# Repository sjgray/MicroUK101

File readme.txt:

MicroUK101
==========

 This is a project to design a board for Grant Searle's Micro UK-101 design.
I started this in 2016 when I was very new at electronics and Kicad.
As I was interested in 6502 and OSI machines I picked this as something to
learn a bit of both things. When I finished the design in Sept 2016 I
ultimately decided not to make boards as I felt I would not really use the
board for anything serious. But it helped spur my interest in designing
more boards. I published the project on my web page and mostly forgot about
it.

 In 2022 I was contacted by someone interested in making the board so I
sent them all the files. Well, they made a run and the board worked with
only one (important) mistake... The power connector was backwards. So, I
have decided to fix that and update a few thing using the latest Kicad
and to put the files on Github for anyone interested in making their own
boards.

You can find my project webpage here:

http://www.cbmsteve.ca/microuk101/index.html

Gerbers files can be found in the Gerbers directory. I have not actually
made boards from these files, so use at your own risk!

Steve

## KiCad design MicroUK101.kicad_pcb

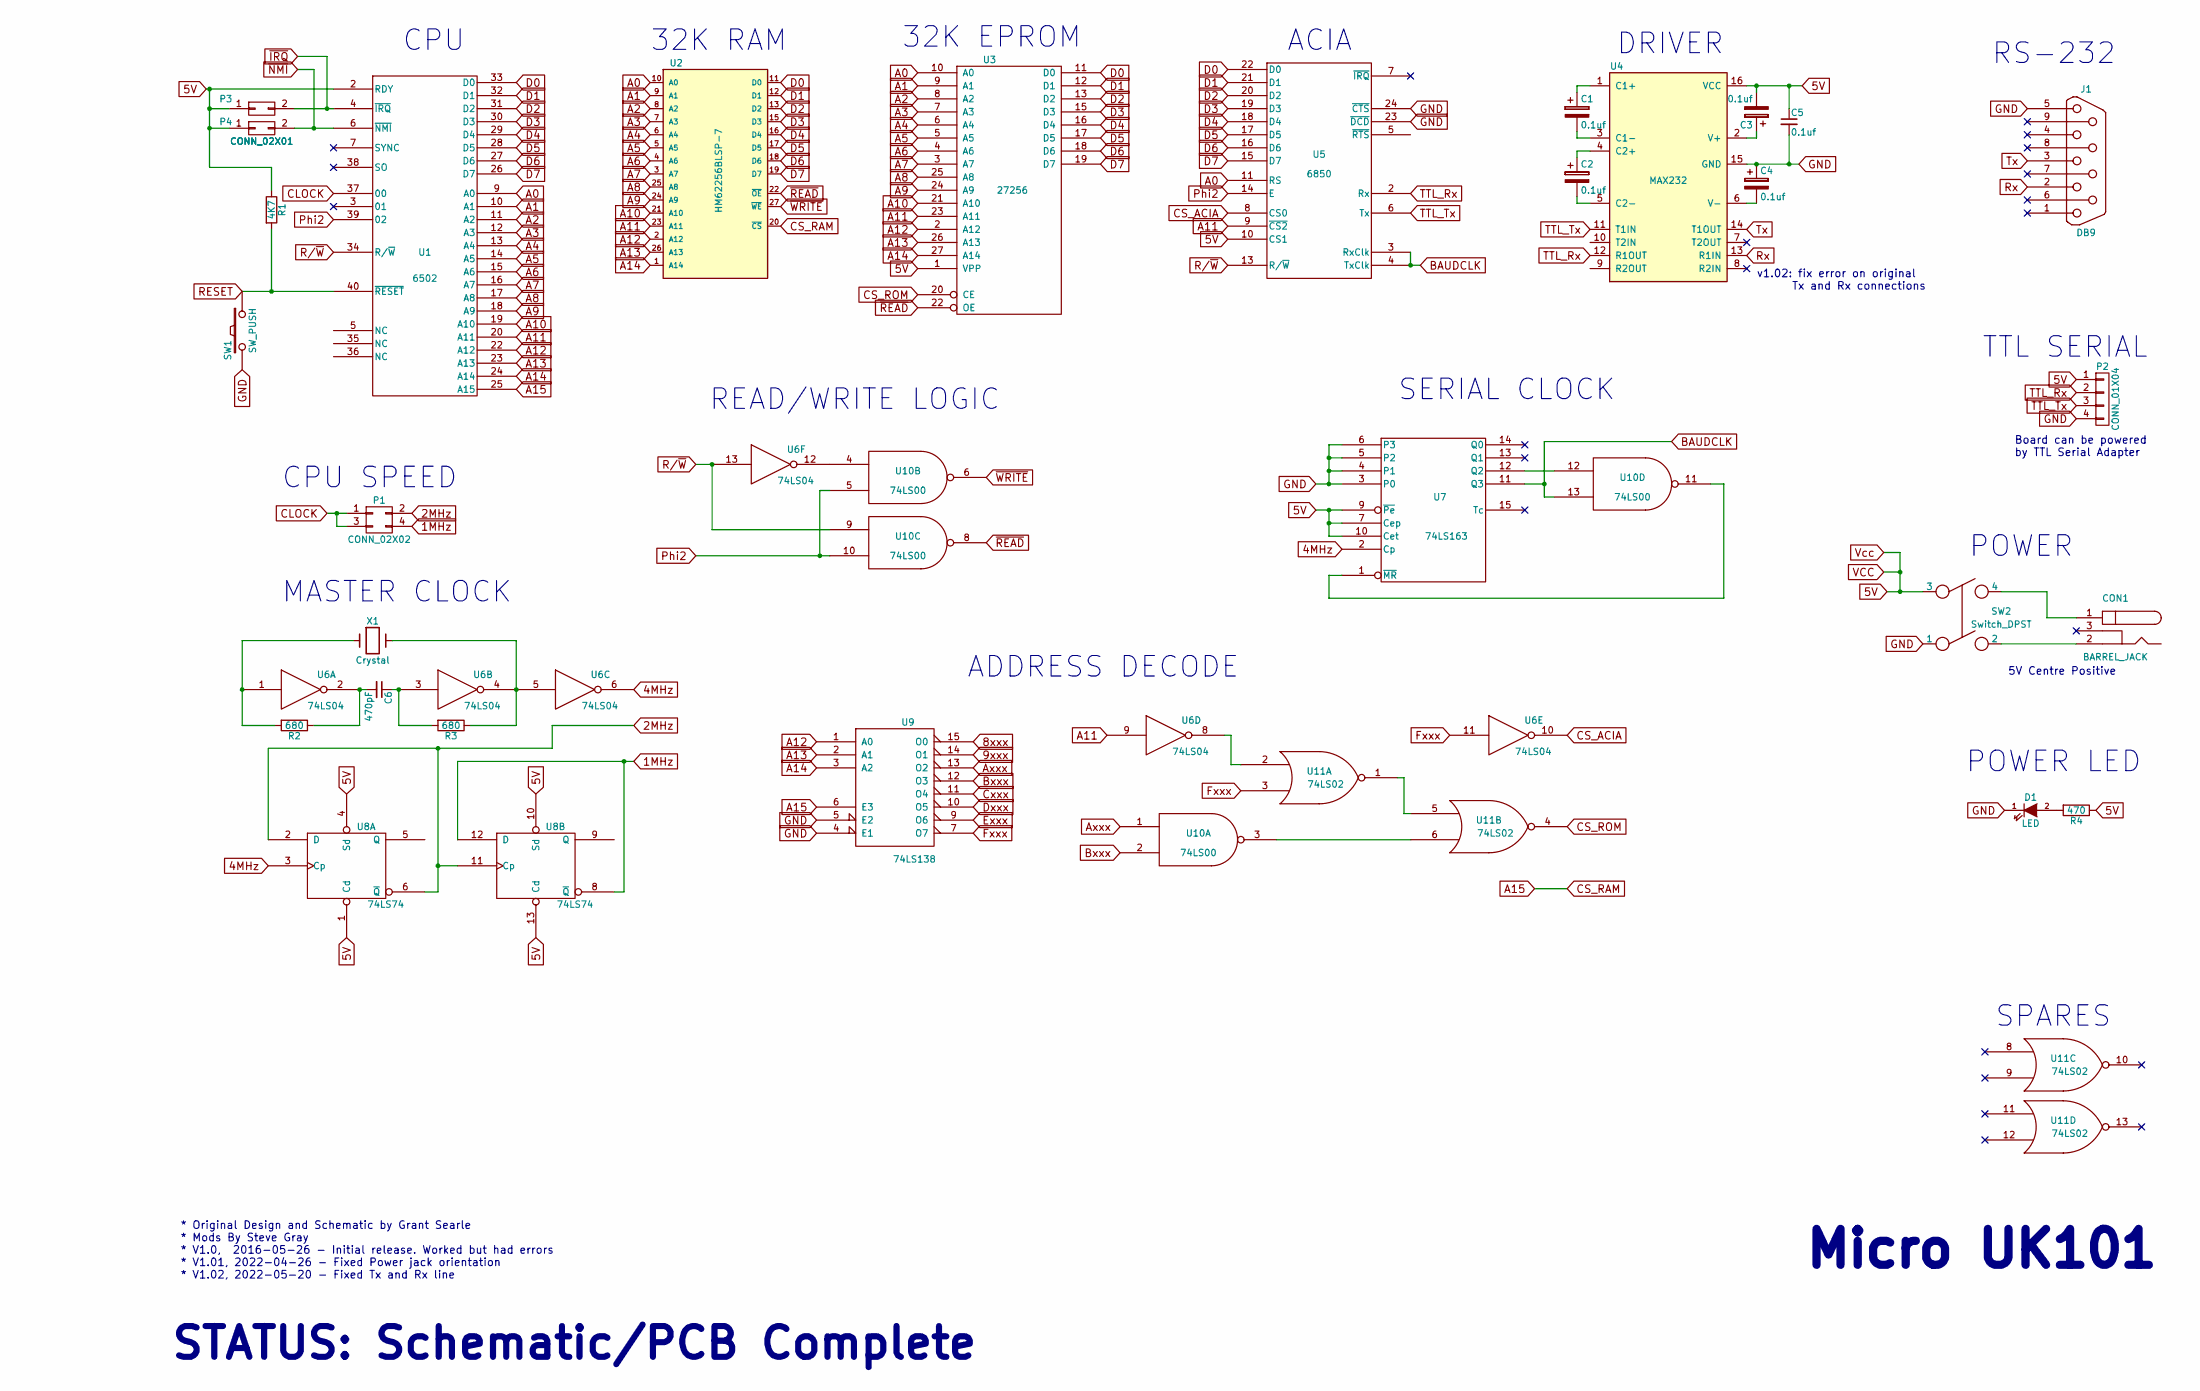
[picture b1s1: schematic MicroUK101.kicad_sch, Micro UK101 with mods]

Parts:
C1, C2, C3, C4: 0.1uf; C_Radial_D5_L6_P2.5
C5: 0.1uf; C_Rect_L4_W2.5_P2.5
C6: 470pF; C_Rect_L4_W2.5_P2.5
CON1: BARREL_JACK
D1: LED; LED-3MM
J1: DB9; DB9MC
P1: CONN_02X02; Pin_Header_Straight_2x02
P2: CONN_01X04; Pin_Header_Straight_1x04
P3, P4: CONN_02X01; Pin_Header_Straight_2x01
R1: 4K7; Resistor_Horizontal_RM10mm
R2, R3: 680; Resistor_Horizontal_RM10mm
R4: 470; Resistor_Horizontal_RM10mm
SW1: SW_PUSH; SW_PUSH_SMALL
SW2: Switch_DPST; SW_TH_Tactile_Omron_B3F-10xx
U1: 6502; DIP-40_W15.24mm_LongPads
U2: HM62256BLSP-7; DIP-28_W15.24mm_LongPads
U3: 27256; DIP-28_W15.24mm_LongPads
U4: MAX232; DIP-16_W7.62mm_LongPads
U5: 6850; DIP-24_W15.24mm_LongPads
U6: 74LS04; DIP-14_W7.62mm_LongPads
U7: 74LS163; DIP-16_W7.62mm_LongPads
U8: 74LS74; DIP-14_W7.62mm_LongPads
U9: 74LS138; DIP-16_W7.62mm_LongPads
U10: 74LS00; DIP-14_W7.62mm_LongPads
U11: 74LS02; DIP-14_W7.62mm_LongPads
X1: Crystal; HC-18UV

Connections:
1MHz: P1.4, U8.8 (~Q), U8.12 (D)
2MHz: P1.2, U8.2 (D), U8.6 (~Q), U8.11 (Cp)
4MHz: U6.6, U7.2 (Cp), U8.3 (Cp)
5V: C3.2, C5.1, P2.1, P3.1, P4.1, R1.1, R4.1, SW2.3, U1.2 (RDY), U1.8 (Vcc), U2.28 (VCC), U3.1 (VPP), U3.28 (VCC), U4.16 (VCC), U5.10 (CS1), U5.12 (Vcc), U6.14 (VCC), U7.7 (Cep), U7.9 (~Pe), U7.10 (Cet), U7.16 (VCC), U8.1 (Cd), U8.4 (Sd), U8.10 (Sd), U8.13 (Cd), U8.14 (VCC), U9.16 (VCC), U10.14 (VCC), U11.14 (VCC)
8xxx: U9.15 (O0)
9xxx: U9.14 (O1)
A0: U1.9 (A0), U2.10 (A0), U3.10 (A0), U5.11 (RS)
A1: U1.10 (A1), U2.9 (A1), U3.9 (A1)
A2: U1.11 (A2), U2.8 (A2), U3.8 (A2)
A3: U1.12 (A3), U2.7 (A3), U3.7 (A3)
A4: U1.13 (A4), U2.6 (A4), U3.6 (A4)
A5: U1.14 (A5), U2.5 (A5), U3.5 (A5)
A6: U1.15 (A6), U2.4 (A6), U3.4 (A6)
A7: U1.16 (A7), U2.3 (A7), U3.3 (A7)
A8: U1.17 (A8), U2.25 (A8), U3.25 (A8)
A9: U1.18 (A9), U2.24 (A9), U3.24 (A9)
A10: U1.19 (A10), U2.21 (A10), U3.21 (A10)
A11: U1.20 (A11), U2.23 (A11), U3.23 (A11), U5.9 (~CS2), U6.9
A12: U1.22 (A12), U2.2 (A12), U3.2 (A12), U9.1 (A0)
A13: U1.23 (A13), U2.26 (A13), U3.26 (A13), U9.2 (A1)
A14: U1.24 (A14), U2.1 (A14), U3.27 (A14), U9.3 (A2)
A15: U1.25 (A15), U2.20 (~CS), U9.6 (E3)
Axxx: U9.13 (O2), U10.1
BAUDCLK: U5.3 (RxClk), U5.4 (TxClk), U7.11 (Q3), U10.13
Bxxx: U9.12 (O3), U10.2
CLOCK: P1.1, P1.3, U1.37 (00)
CS_ACIA: U5.8 (CS0), U6.10
CS_ROM: U3.20 (CE), U11.4
Cxxx: U9.11 (O4)
D0: U1.33 (D0), U2.11 (D0), U3.11 (D0), U5.22 (D0)
D1: U1.32 (D1), U2.12 (D1), U3.12 (D1), U5.21 (D1)
D2: U1.31 (D2), U2.13 (D2), U3.13 (D2), U5.20 (D2)
D3: U1.30 (D3), U2.15 (D3), U3.15 (D3), U5.19 (D3)
D4: U1.29 (D4), U2.16 (D4), U3.16 (D4), U5.18 (D4)
D5: U1.28 (D5), U2.17 (D5), U3.17 (D5), U5.17 (D5)
D6: U1.27 (D6), U2.18 (D6), U3.18 (D6), U5.16 (D6)
D7: U1.26 (D7), U2.19 (D7), U3.19 (D7), U5.15 (D7)
Dxxx: U9.10 (O5)
Exxx: U9.9 (O6)
Fxxx: U6.11, U9.7 (O7), U11.3
GND: C4.1, C5.2, D1.1 (K), J1.5, P2.4, SW1.2, SW2.1, U1.21 (GND), U2.14 (GND), U3.14 (GND), U4.15 (GND), U5.1 (GND), U5.23 (~DCD), U5.24 (~CTS), U6.7 (GND), U7.3 (P0), U7.4 (P1), U7.5 (P2), U7.6 (P3), U7.8 (GND), U8.7 (GND), U9.4 (E1), U9.5 (E2), U9.8 (GND), U10.7 (GND), U11.7 (GND)
unnamed: C1.1, U4.1 (C1+)
unnamed: C1.2, U4.3 (C1-)
unnamed: C2.1, U4.4 (C2+)
unnamed: C2.2, U4.5 (C2-)
unnamed: C3.1, U4.2 (V+)
unnamed: C4.2, U4.6 (V-)
unnamed: C6.1, R3.2, U6.3
unnamed: C6.2, R2.1, U6.2
unnamed: CON1.1, SW2.4
unnamed: CON1.2, SW2.2
unnamed: D1.2 (A), R4.2
unnamed: R2.2, U6.1, X1.1
unnamed: R3.1, U6.4, U6.5, X1.2
unnamed: U10.3, U11.6
unnamed: U6.12, U10.4
unnamed: U7.1 (~MR), U10.11
unnamed: U7.12 (Q2), U10.12
unnamed: U11.1, U11.5
unnamed: U6.8, U11.2
Phi2: U1.39 (02), U5.14 (E), U10.5, U10.10
RESET: R1.2, SW1.1, U1.40 (~RESET)
Rx: J1.2, U4.13 (R1IN)
R/~W: U1.34 (R/~W), U5.13 (R/~W), U6.13, U10.9
TTL_Rx: P2.2, U4.12 (R1OUT), U5.2 (Rx)
TTL_Tx: P2.3, U4.11 (T1IN), U5.6 (Tx)
Tx: J1.3, U4.14 (T1OUT)
VSS: U1.1 (VSS)
~IRQ: P3.2, U1.4 (~IRQ)
~NMI: P4.2, U1.6 (~NMI)
~READ: U2.22 (~OE), U3.22 (OE), U10.8
~WRITE: U2.27 (~WE), U10.6

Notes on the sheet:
Micro UK101
CPU
POWER
READ/WRITE LOGIC
* Original Design and Schematic by Grant Searle * Mods By Steve Gray * V1.0, 2016-05-26 - Initial release. Worked but had errors * V1.01, 2022-04-26 - Fixed Power jack orientation * V1.02, 2022-05-20 - Fixed Tx and Rx line
MASTER CLOCK
DRIVER
STATUS: Schematic/PCB Complete
32K EPROM
Board can be powered by TTL Serial Adapter
SPARES
POWER LED
TTL SERIAL
RS-232
ACIA
ADDRESS DECODE
32K RAM
SERIAL CLOCK
v1.02: fix error on original Tx and Rx connections
5V Centre Positive
CPU SPEED

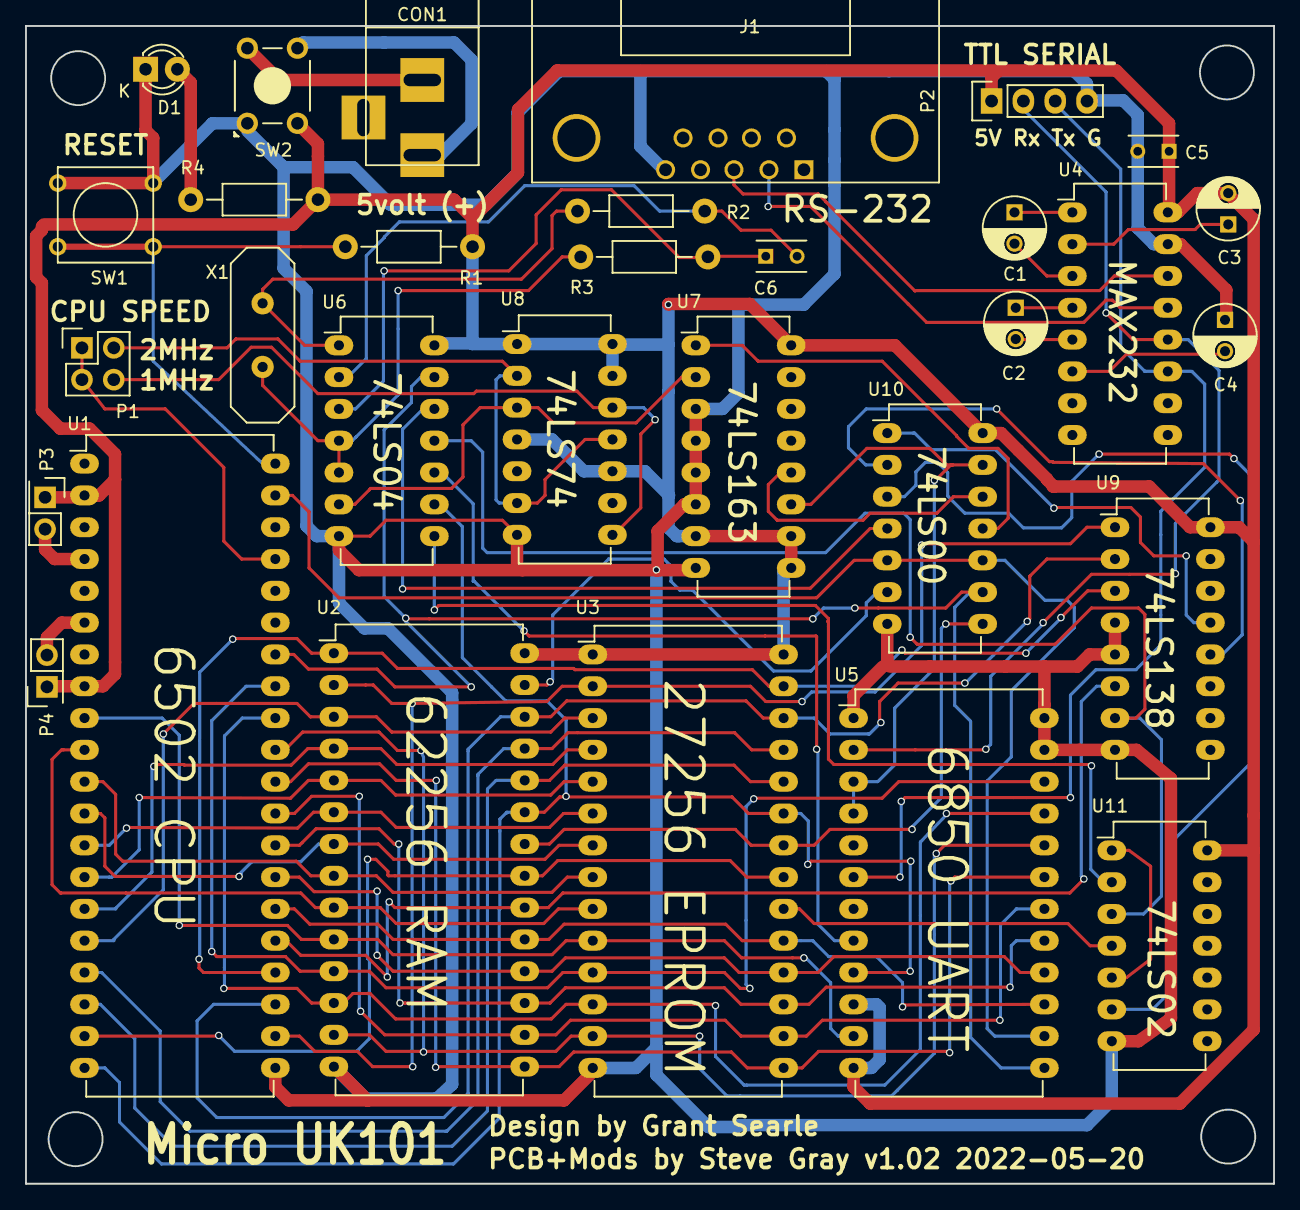
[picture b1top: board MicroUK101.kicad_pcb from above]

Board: 2 copper layers, 99.7 x 92.5 mm, 31 parts (0 on the bottom side), 66 nets.

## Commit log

2022-04-19 :octocat: Added .gitattributes & .gitignore files
2022-04-19 Initial V1.0 release
    This was designed in 2016 but never officially released. I have
    corrected a few things and saved the files in the latest Kicad v6.
    Gerbers are included. The schematic design was verified working, however
    the inital pcb had an error with the power connector orientation. That
    has been fixed. Gerbers have not been verified so USE AT OWN RISK!
2022-04-25 Update to add missing gerber files
    Solder Masks now included.
2022-04-25 Clean up a big mess
    Gerbers directory should have the correct files now.
    Backup contains only zipped backup. Removed many duplicates. Sorry.
2022-05-21 Release 1.02
    Fix Tx and Rx lines to RS-232. Ran DRC and fixed a bunch of small track
    errors. Updated silkscreen, created new gerbers.
2025-01-15 Update webpage
    http://www.cbmsteve.ca/
